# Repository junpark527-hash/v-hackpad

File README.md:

## Materials for a Hackpad, only need PCB and Case 

Custom macropad parts, built for the NASA x Hack Club Stardance Challenge.

# About

This is my second project related to a hackpad this summer and I have faced severely less difficulties than my first time. I am glad that I was able to retain most of the skills I learned previously and use them again. My build consists of an encoder, some keys, and a case.

# Features:
* a 2-part case (3D printed)
* EC11 Rotary encoder
* 3 keys/switches
* 4 M2 heatset inserts and screws

# CAD Model

This case has 2 separate parts: one for the bottom of the case and one for the top. The top part consists of the cutouts for my switches and encoder, and the other half is the bottom of my case. I am planning on assembling the case together using M2-Heatset inserts and screws on each corner. It also has 4 small raised pillars in the bottom of the case for my pcb to rest on. Additionally, I made a cutout for the USB on the case.

# Schematic
This is my Schematic: 

# PCB
This is my PCB: 

# BOM
This is everything that should be needed to make this hackpad: 

* 3x Cherry MX-style Switches
* 3x White Blank DSA Keycaps
* 4x M3x5x4mm Heatset inserts
* 4x M3x16mm Screws
* 1x EC11 Rotary Encoder
* 1x XIAO RP2040
* 1x Case (2 printed parts)

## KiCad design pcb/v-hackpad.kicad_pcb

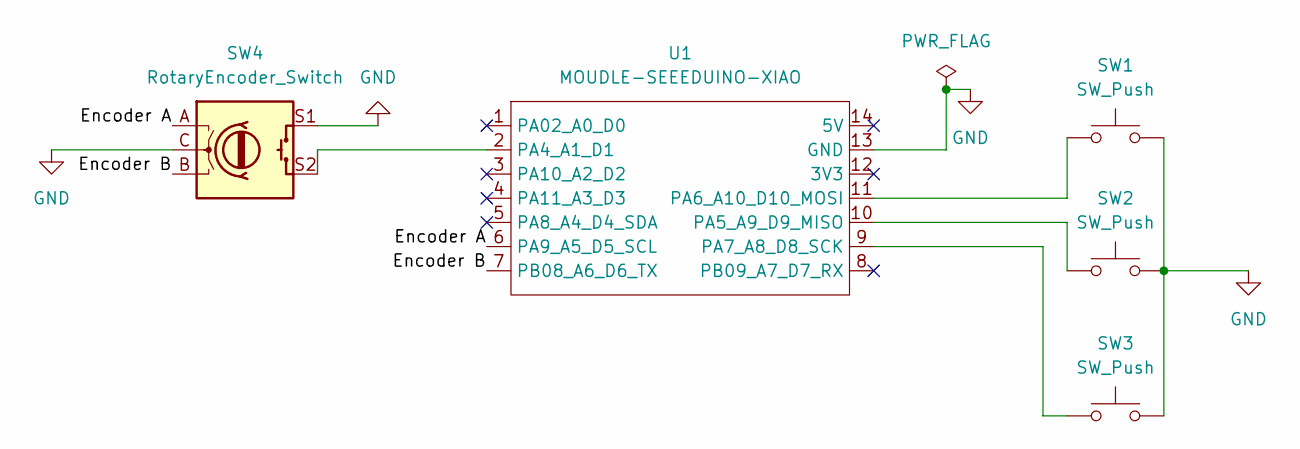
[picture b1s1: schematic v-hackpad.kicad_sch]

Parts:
SW1, SW2, SW3: SW_Push; SW_Cherry_MX_1.00u_PCB
SW4: RotaryEncoder_Switch; RotaryEncoder_Alps_EC11E-Switch_Vertical_H20mm
U1: MOUDLE-SEEEDUINO-XIAO; XIAO-Generic-Hybrid-14P-2.54-21X17.8MM

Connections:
/Encoder A: SW4.A, U1.6 (PA9_A5_D5_SCL)
/Encoder B: SW4.B, U1.7 (PB08_A6_D6_TX)
GND: SW1.2, SW2.2, SW3.2, SW4.C, SW4.S1, U1.13 (GND)
unnamed: SW4.S2, U1.2 (PA4_A1_D1)
unnamed: SW2.1, U1.10 (PA5_A9_D9_MISO)
unnamed: SW1.1, U1.11 (PA6_A10_D10_MOSI)
unnamed: SW3.1, U1.9 (PA7_A8_D8_SCK)

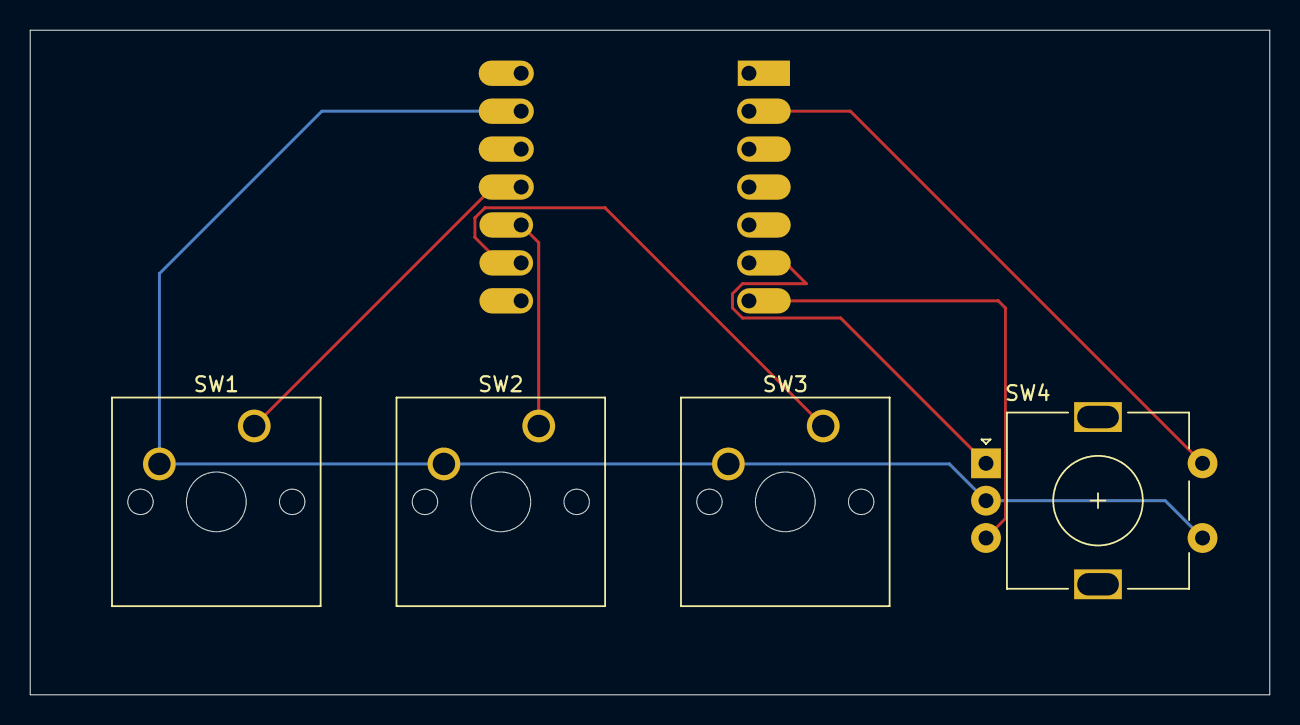
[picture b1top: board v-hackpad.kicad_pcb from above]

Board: 2 copper layers, 83.0 x 44.5 mm, 5 parts (1 on the bottom side), 7 nets.
